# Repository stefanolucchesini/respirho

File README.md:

# RespirHo' Project

This repository contains all the necessary files to program the firmware of RespirHo' boards and acquire the respiratory signal.

Repo structure:
* Folder "ANT_PROVA-SDK_PC.3.5_CONSALVATAGGIO" contains the old ANT interface.
* Folder "ANT_STE" contains the renewed ANT interface with new functions like sensors calibration, acquisition stop and resume.
* Folder "File HEX" contains the binary files to upload on boards. Upload "Device_x.hex" (with x: 1,2,3) on PCB version, "Device_x_(millefori).hex" (with x: 1,2,3) for prototype.
* Folder "nRF5_SDK_14.2.0_17b948a" contains the software development kit for the nRF52832 microcontroller. 
* Folder "OTA_Updater_v1.4" contains an app that allows to upload new firmware to boards over the air (OTA).

Please refer to the [developer guide](https://drive.google.com/file/d/1UFlXrOAoPOUmqghLcS6q3u2aQWWckizt/view?usp=sharing) for further information about usage.

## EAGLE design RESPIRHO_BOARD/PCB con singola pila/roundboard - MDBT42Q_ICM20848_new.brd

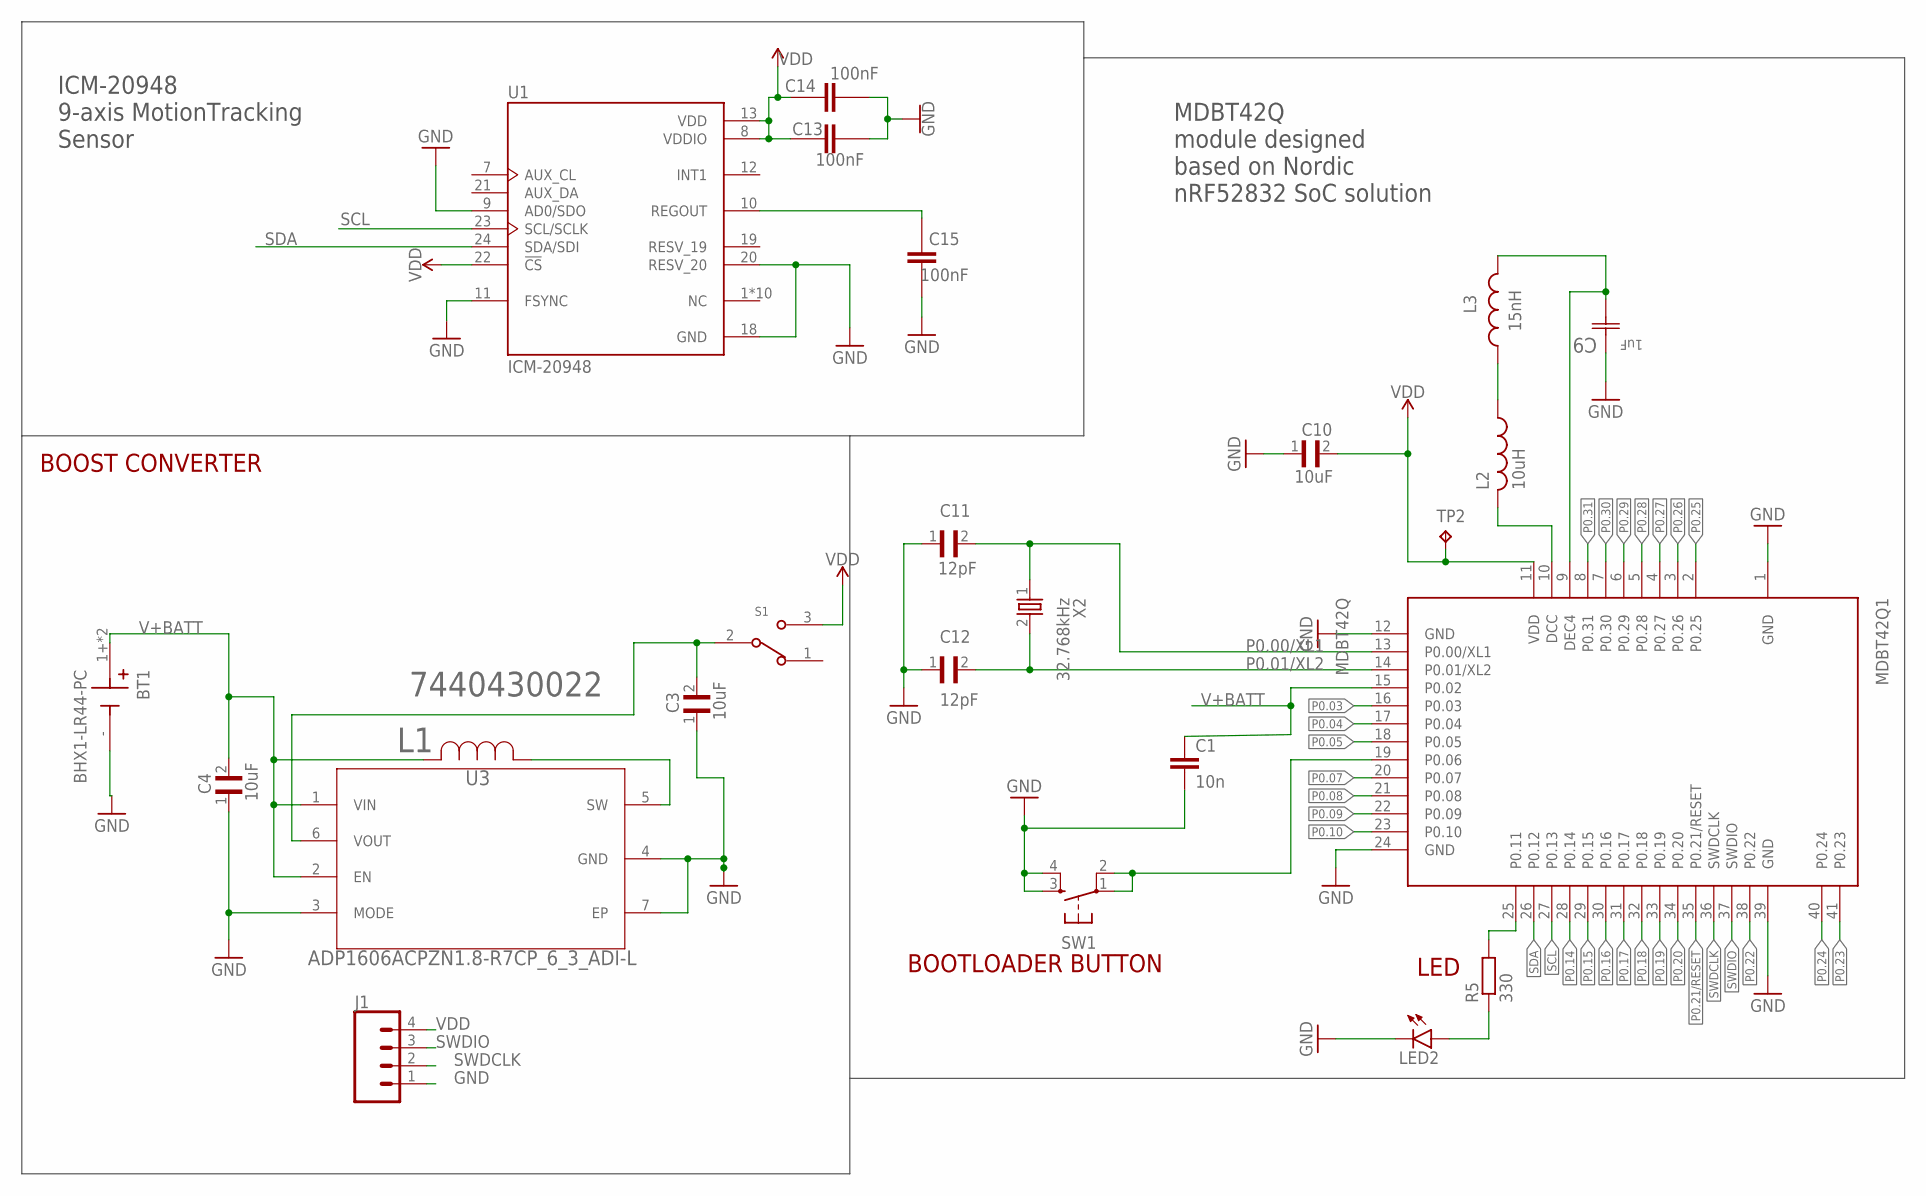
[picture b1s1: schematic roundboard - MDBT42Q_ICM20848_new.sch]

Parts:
BT1: BHX1-LR44-PC; BAT_BHX1-LR44-PC
C1: 10n; C0603
C3, C4, C10: 10uF; CAPC1608X95N
C9: 1uF; CAPC1608X90N
C11, C12: 12pF; CAPC1005X56N
C13, C14, C15: 100nF; CAPC1005X60
J1: CONN_04PTH; 1X04
L1: 7440430022; IND_7440430022_WRE
L2: 10uH; RESC0603_L
L3: 15nH; INDC1005X55N
LED2: LEDCHIPLED_0603; CHIPLED_0603
MDBT42Q1: MDBT42Q
R5: 330; R0603
S1: JS102011SAQN; SW_JS102011SAQN
SW1: SWITCH_SPST_4_PINRECT; TACTILE_SWITCH_SMD_4.6X2.8MM
TP2: TPB1,27; B1,27
U1: ICM-20948; QFN40P300X300X105-24N
U3: ADP1606ACPZN1.8-R7CP_6_3_ADI-L; CP_6_3_ADI-L
X2: 32.768kHz; XTAL_3215_N

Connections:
GND: BT1.-, C1.2, C3.1, C4.1, C9.1 (C1), C10.1, C11.1, C12.1, C13.1, C14.1, C15.1, J1.1, LED2.C, MDBT42Q1.1 (GND), MDBT42Q1.12 (GND), MDBT42Q1.24 (GND), MDBT42Q1.39 (GND), SW1.3, SW1.4, U1.9 (AD0/SDO), U1.11 (FSYNC), U1.18 (GND), U1.20 (RESV_20), U3.3 (MODE), U3.4 (GND), U3.7 (EP)
IND: L1.1, U3.5 (SW)
unnamed: LED2.A, R5.1
unnamed: L2.2, MDBT42Q1.10 (DCC)
unnamed: L2.1, L3.1
unnamed: C9.2 (C2), L3.2, MDBT42Q1.9 (DEC4)
unnamed: MDBT42Q1.25 (P0.11), R5.2
unnamed: C15.2, U1.10 (REGOUT)
P0.00/XL1: C11.2, MDBT42Q1.13 (P0.00/XL1), X2.1
P0.01/XL2: C12.2, MDBT42Q1.14 (P0.01/XL2), X2.2
P0.03: MDBT42Q1.16 (P0.03)
P0.04: MDBT42Q1.17 (P0.04)
P0.05: MDBT42Q1.18 (P0.05)
P0.07: MDBT42Q1.20 (P0.07)
P0.08: MDBT42Q1.21 (P0.08)
P0.09: MDBT42Q1.22 (P0.09)
P0.10: MDBT42Q1.23 (P0.10)
P0.14: MDBT42Q1.28 (P0.14)
P0.15: MDBT42Q1.29 (P0.15)
P0.16: MDBT42Q1.30 (P0.16)
P0.17: MDBT42Q1.31 (P0.17)
P0.18: MDBT42Q1.32 (P0.18)
P0.19: MDBT42Q1.33 (P0.19)
P0.20: MDBT42Q1.34 (P0.20)
P0.21/RESET: MDBT42Q1.35 (P0.21/RESET)
P0.22: MDBT42Q1.38 (P0.22)
P0.23: MDBT42Q1.41 (P0.23)
P0.24: MDBT42Q1.40 (P0.24)
P0.25: MDBT42Q1.2 (P0.25)
P0.26: MDBT42Q1.3 (P0.26)
P0.27: MDBT42Q1.4 (P0.27)
P0.28: MDBT42Q1.5 (P0.28)
P0.29: MDBT42Q1.6 (P0.29)
P0.30: MDBT42Q1.7 (P0.30)
P0.31: MDBT42Q1.8 (P0.31)
P06: MDBT42Q1.19 (P0.06), SW1.1, SW1.2
SCL: MDBT42Q1.27 (P0.13), U1.23 (SCL/SCLK)
SDA: MDBT42Q1.26 (P0.12), U1.24 (SDA/SDI)
SW: C3.2, S1.2, U3.6 (VOUT)
SWDCLK: J1.2, MDBT42Q1.36 (SWDCLK)
SWDIO: J1.3, MDBT42Q1.37 (SWDIO)
V+BATT: BT1.1+ (+), BT1.2+ (+), C1.1, C4.2, L1.2, MDBT42Q1.15 (P0.02), U3.1 (VIN), U3.2 (EN)
VDD: C10.2, C13.2, C14.2, J1.4, MDBT42Q1.11 (VDD), S1.3, TP2.TP, U1.8 (VDDIO), U1.13 (VDD), U1.22 (!CS)

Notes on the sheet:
ICM-20948 9-axis MotionTracking Sensor
MDBT42Q module designed based on Nordic nRF52832 SoC solution
LED
BOOTLOADER BUTTON
BOOST CONVERTER

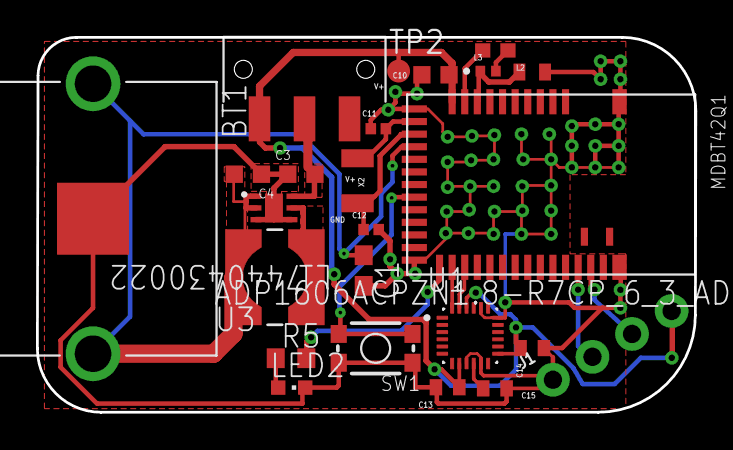
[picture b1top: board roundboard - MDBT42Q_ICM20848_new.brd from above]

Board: 2 copper layers, 36.6 x 20.8 mm, 24 parts (0 on the bottom side), 18 nets.

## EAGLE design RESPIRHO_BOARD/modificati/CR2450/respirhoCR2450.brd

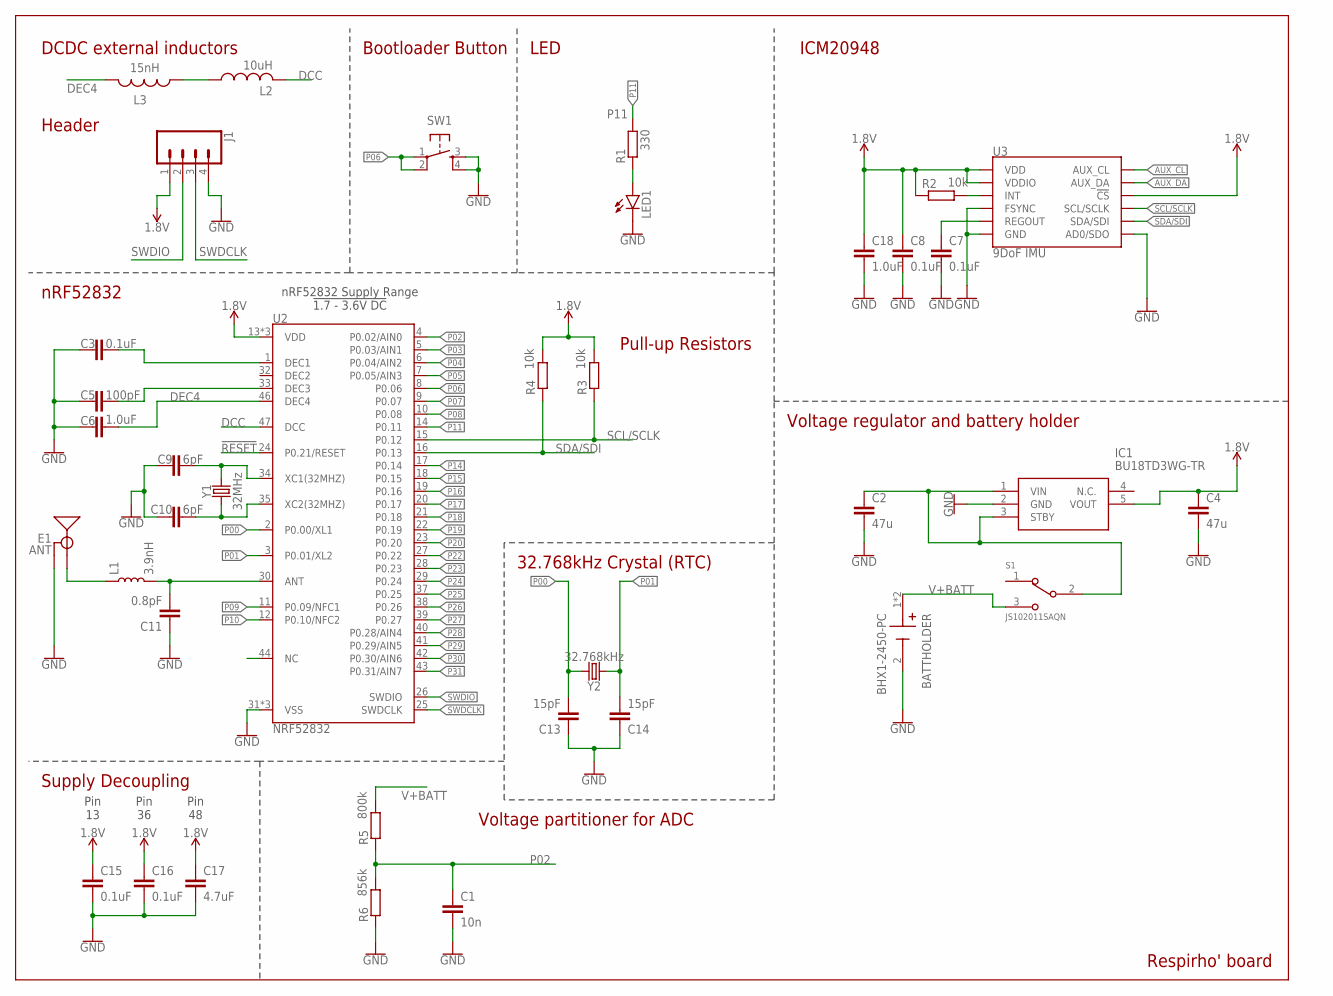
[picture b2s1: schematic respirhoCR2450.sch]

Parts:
BATTHOLDER: BHX1-2450-PC; BAT_BHX1-2450-PC
C1: 10n; C1206
C2, C4: 47u; C1206
C3, C15, C16: 0.1uF; 0402
C5: 100pF; 0402
C6: 1.0uF; 0402
C7, C8: 0.1uF; 0603
C9, C10: 6pF; 0402
C11: 0.8pF; 0402
C13, C14: 15pF; 0402
C17: 4.7uF; 0603
C18: 1.0uF; 0603
E1: ANT; TRACE_ANTENNA_2.4GHZ_15.2MM
IC1: BU18TD3WG-TR; SOT95P280X125-5N
J1: CONN_04PTH; 1X04
L1: 3.9nH; 0402
L2: 10uH; RESC0603_L
L3: 15nH; INDC1005X55N
LED1: LEDCHIPLED_1206; CHIPLED_1206
R1: 330; R0805
R2, R3, R4: 10k; R0805
R5: 800k; R0805
R6: 856k; R0805
S1: JS102011SAQN; SW_JS102011SAQN
SW1: SWITCH_SPST_4_PINRECT; TACTILE_SWITCH_SMD_4.6X2.8MM
U2: NRF52832; QFN48-6X6MM
U3: 9DoF IMU; QFN24-3X3
Y1: 32MHz; CRYSTAL-SMD-2.0X1.6MM
Y2: 32.768kHz; CRYSTAL-SMD-3.2X1.5MM

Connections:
1.8V: C4.1, C8.1, C15.1, C16.1, C17.1, C18.1, IC1.5 (VOUT), J1.1, R2.1, R3.2, R4.2, U2.13 (VDD), U2.36 (VDD), U2.48 (VDD), U3.8 (VDDIO), U3.13 (VDD), U3.22 (!CS)
!RESET!: U2.24 (P0.21/RESET)
ANT: C11.2, L1.2, U2.30 (ANT)
AUX_CL: U3.7 (AUX_CL)
AUX_DA: U3.21 (AUX_DA)
DCC: L2.2, U2.47 (DCC)
DEC1: C3.2, U2.1 (DEC1)
DEC3: C5.2, U2.33 (DEC3)
DEC4: C6.2, L3.2, U2.46 (DEC4)
GND: BATTHOLDER.2 (-), C1.2, C2.2, C3.1, C4.2, C5.1, C6.1, C7.2, C8.2, C9.1, C10.2, C11.1, C13.1, C14.1, C15.2, C16.2, C17.2, C18.2, E1.GND, IC1.2 (GND), J1.4, LED1.C, R6.1, SW1.3, SW1.4, U2.31 (VSS), U2.45 (VSS), U2.EP (VSS), U3.9 (AD0/SDO), U3.11 (FSYNC), U3.18 (GND), U3.20 (GND)
unnamed: LED1.A, R1.1
unnamed: C7.1, U3.10 (REGOUT)
unnamed: R2.2, U3.12 (INT)
unnamed: C2.1, IC1.1 (VIN), IC1.3 (STBY), S1.2
unnamed: L2.1, L3.1
unnamed: E1.ANT (SIGNAL), L1.1
NC: U2.44 (NC)
P00: C13.2, U2.2 (P0.00/XL1), Y2.P$2 (2)
P01: C14.2, U2.3 (P0.01/XL2), Y2.P$1 (1)
P02: C1.1, R5.1, R6.2, U2.4 (P0.02/AIN0)
P03: U2.5 (P0.03/AIN1)
P04: U2.6 (P0.04/AIN2)
P05: U2.7 (P0.05/AIN3)
P06: SW1.1, SW1.2, U2.8 (P0.06)
P07: U2.9 (P0.07)
P08: U2.10 (P0.08)
P09: U2.11 (P0.09/NFC1)
P10: U2.12 (P0.10/NFC2)
P11: R1.2, U2.14 (P0.11)
P14: U2.17 (P0.14)
P15: U2.18 (P0.15)
P16: U2.19 (P0.16)
P17: U2.20 (P0.17)
P18: U2.21 (P0.18)
P19: U2.22 (P0.19)
P20: U2.23 (P0.20)
P22: U2.27 (P0.22)
P23: U2.28 (P0.23)
P24: U2.29 (P0.24)
P25: U2.37 (P0.25)
P26: U2.38 (P0.26)
P27: U2.39 (P0.27)
P28: U2.40 (P0.28/AIN4)
P29: U2.41 (P0.29/AIN5)
P30: U2.42 (P0.30/AIN6)
P31: U2.43 (P0.31/AIN7)
SCL/SCLK: R3.1, U2.15 (P0.12), U3.23 (SCL/SCLK)
SDA/SDI: R4.1, U2.16 (P0.13), U3.24 (SDA/SDI)
SWDCLK: J1.3, U2.25 (SWDCLK)
SWDIO: J1.2, U2.26 (SWDIO)
V+BATT: BATTHOLDER.1 (+), BATTHOLDER.1_1 (+), R5.2, S1.3
XC1: C9.2, U2.34 (XC1(32MHZ)), Y1.3 (2)
XC2: C10.1, U2.35 (XC2(32MHZ)), Y1.1

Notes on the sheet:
Pin 13
Pin 36
Pin 48
DCDC external inductors
Bootloader Button
LED
nRF52832
32.768kHz Crystal (RTC)
Supply Decoupling
nRF52832 Supply Range !1.7 - 3.6V DC!
ICM20948
Respirho' board
Voltage regulator and battery holder
Voltage partitioner for ADC
Header
Pull-up Resistors

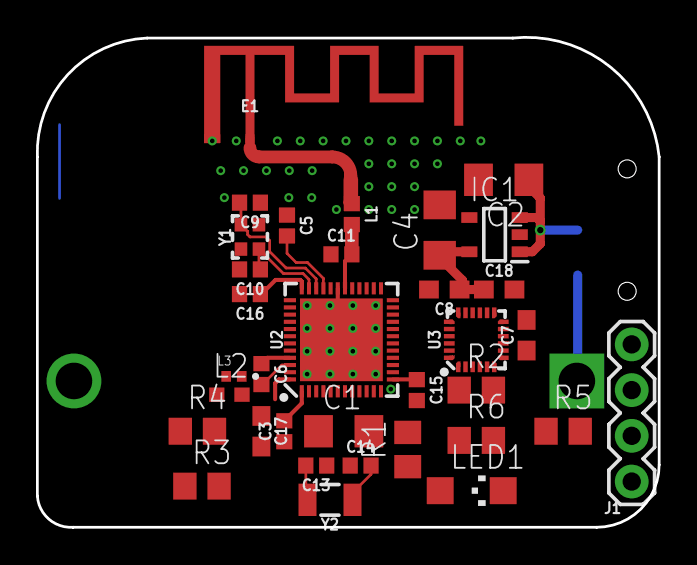
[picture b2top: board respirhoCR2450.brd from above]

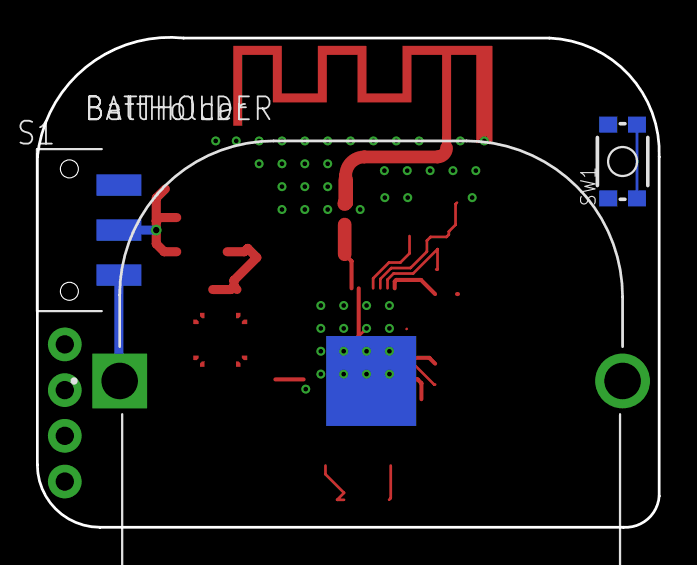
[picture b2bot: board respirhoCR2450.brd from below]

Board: 2 copper layers, 34.5 x 27.2 mm, 37 parts (3 on the bottom side), 25 nets.

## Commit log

2021-03-09 Implementata acquisizione multipla senza spegnere e riaccendere l'unità. Progetto keil unico. Lettura tensione della batteria e invio nel payload ant. Esecuzione della lettura dei valori dell'IMU con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
2021-03-09 Aggiunta cartella con codice modificato per chiavetta ANT: Con il tasto "f" si ferma l'acquisizione, non è più necessario premere 0 e invio, basta mettere il nome del file che si vuole creare
2021-03-09 Modificato codice per chiavetta ant: per interrompere l'acquisizione si preme f+invio (invia messaggio alle unità che dice di fermarsi) e poi q.+invio Verrà richiesto se si vuole terminare l'acquisiz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
2021-03-11 Aggiunto qualche commento al main, tutto testato e funzionante.
2021-03-18 Added gitignore and some modification to eagle files
2021-03-18 tolti file inutili con gitignore
2021-03-18 aggiunti file hex ed exe
2021-03-20 Aggiunto qualche commento
    e log nel main
2021-03-20 aggiunta funzione calibrazione
    Però bisogna trovare un modo di salvare i dati nella flash
2021-03-20 Attesa licenza completa....
2021-03-20 Revert "Aggiunto qualche commento"
    This reverts commit d13a46a695195c3d540f15c2f1392308871244a6.
2021-03-23 Revert "Attesa licenza completa...."
    This reverts commit ffb6cbb24ab223828acb1e865ad0a34fb308eeaf.
2021-03-23 Aggiunto clear del buffer messaggi ANT
    Quando viene interrotta la acquisizione il buffer dei quaternioni da inviare viene svuotato.
    La calibrazione automatica sembra funzionare, ora viene eseguita ogni volta all'accensione dopo il messaggio: " Attesa messaggio di inizio aquisizione", andrebbe messa in una funzione apposita e i da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
2021-03-27 Aggiunta scheda EAGLE
2021-03-28 Updated gitignore
2021-03-28 Calibrazione funzionante
    ma i dati vengono salvati solo nella RAM
2021-03-28 Board spostata in altra repository
2021-03-28 Calibrazione con dati salvati su vettori, aggiunta funzione per scegliere potenza di trasmissione
    Bisogna implementare un comando da chiavetta ANT (e nel firmware nrf) per far partire la calibrazione e volendo anche dei comandi per scegliere la potenza di trasmissione. Adesso la potenza è al live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
    Il codice è stato testato, la trasmissione funziona, la calibrazione va controllata quando si farà un comando apposito, ma da debug sembra funzionare perchè i dati negli array cambiano
2021-03-29 Aggiunte funzioni a chiavetta ANT
    Ora dice il tempo di acquisizione in secondi, il numero di campioni ricevuti dalle unità e quanti sarebbero dovuti essere i campioni ricevuti
2021-04-05 Calibrazione automatica con salvataggio in flash + comando chiavetta ANT
    Il sistema non è ancora completamente testato. Inoltre ora si usa l'app_timer al posto del simple timer, dovrebbe far risparmiare un po' di energia perchè fa uso dell'oscillatore esterno e non del cl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
2021-04-28 All'accensione invia anche tensione Vdd (ultimo byte). Aggiunto OTA updater
2021-04-29 Output a schermo e su file alleggerito, la modalità verbosa (stampa tutti i Tx: ... ) si può attivare col tasto v
2021-05-02 Chiavetta ANT: nuovo modo di generare i file .txt, introduzione automatica di marker per dati persi
2021-05-06 Cambiati pin I2C per avere i soliti della board
2021-06-26 Aggiunti timestamps ai campioni ricevuti (UNIX TIME), modalità verbosa non aggiunge tx:... a file
2021-06-28 timestamp in millisecondi
2021-06-28 tolti file inutili
2021-06-29 stampa punti durante la configurazione del canale ANT
2021-07-01 generazione file di report acquisizione
2021-07-05 riapertura canale ANT in caso di timeout
2021-07-08 tolti file file inutili
2021-07-11 aggiunta campioni mancanti anche oltre i 25 secondi di timeout
2021-07-14 Possibilità (brutale) di escludere magnetometro, nuovo firmware con magnetometro escluso
2021-07-16 migliorato algoritmo di aggiunta campioni persi
2021-07-25 Corretto parametro di FSR nella calibrazione
2021-08-08 corretto errore di calibrazione (offset va sottratto, non aggiunto)

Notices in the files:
parts and their libraries:
SparkFun-Electromechanical: Licensing: Creative Commons ShareAlike 4.0 International - https://creativecommons.org/licenses/by-sa/4.0
COPYRIGHT: Copyright (C) 2018 Accelerated Designs. All rights reserved
